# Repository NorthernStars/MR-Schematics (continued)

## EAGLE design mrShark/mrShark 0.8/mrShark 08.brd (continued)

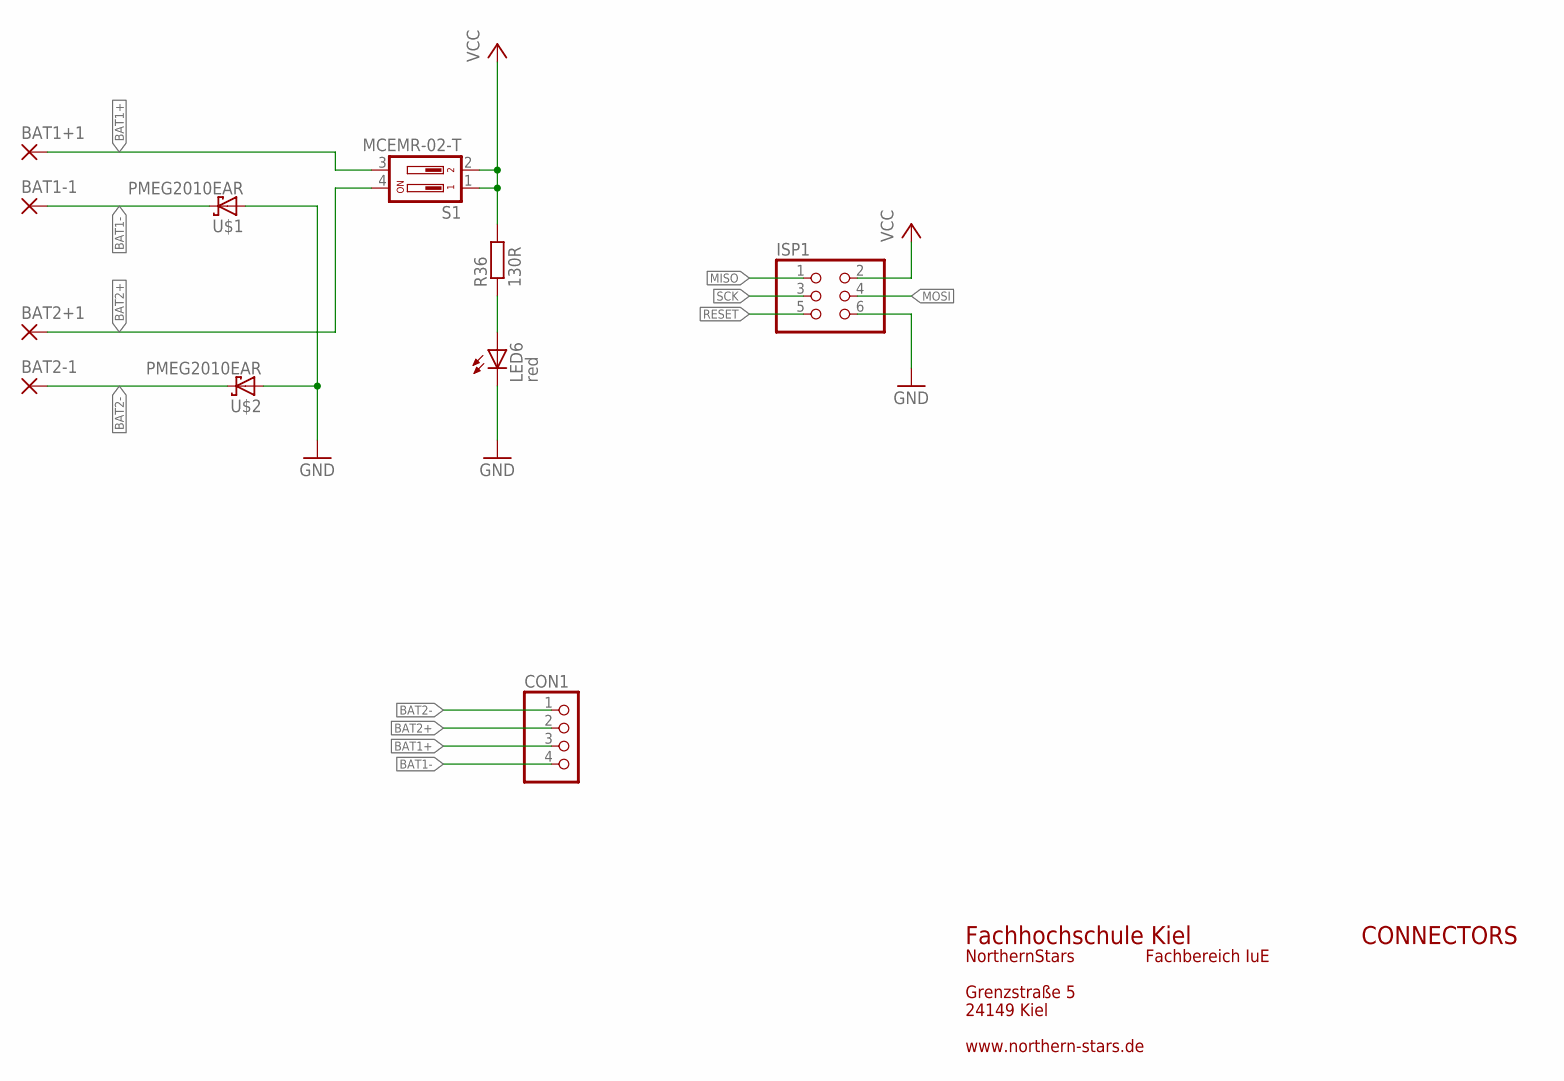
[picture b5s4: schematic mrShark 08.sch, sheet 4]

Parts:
BAT1+1, BAT1-1, BAT2+1, BAT2-1: 1,6/0,9
CON1: PINHD-1X04_2.54-SMD-90°; 1X04SMD/90
ISP1: PINHD-2X03_2.54-SMD; 2X03SMD
LED6: red; CHIPLED_1206
R36: 130R; R1206
S1: MCEMR-02-T; CTS-219-02
U$1, U$2: PMEG2010EAR; SOD323-R

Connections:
BAT1+: BAT1+1.1, CON1.3, S1.3
BAT1-: BAT1-1.1, CON1.4, U$1.C
BAT2+: BAT2+1.1, CON1.2, S1.4
BAT2-: BAT2-1.1, CON1.1, U$2.C
GND: ISP1.6, LED6.C, U$1.A, U$2.A; also elsewhere on the board
MISO: ISP1.1; also elsewhere on the board
MOSI: ISP1.4; also elsewhere on the board
unnamed: LED6.A, R36.1
RESET: ISP1.5; also elsewhere on the board
SCK: ISP1.3; also elsewhere on the board
VCC: ISP1.2, R36.2, S1.1, S1.2; also elsewhere on the board

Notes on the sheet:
CONNECTORS
Fachhochschule Kiel
Grenzstraße 5
24149 Kiel
NorthernStars
Fachbereich IuE
www.northern-stars.de

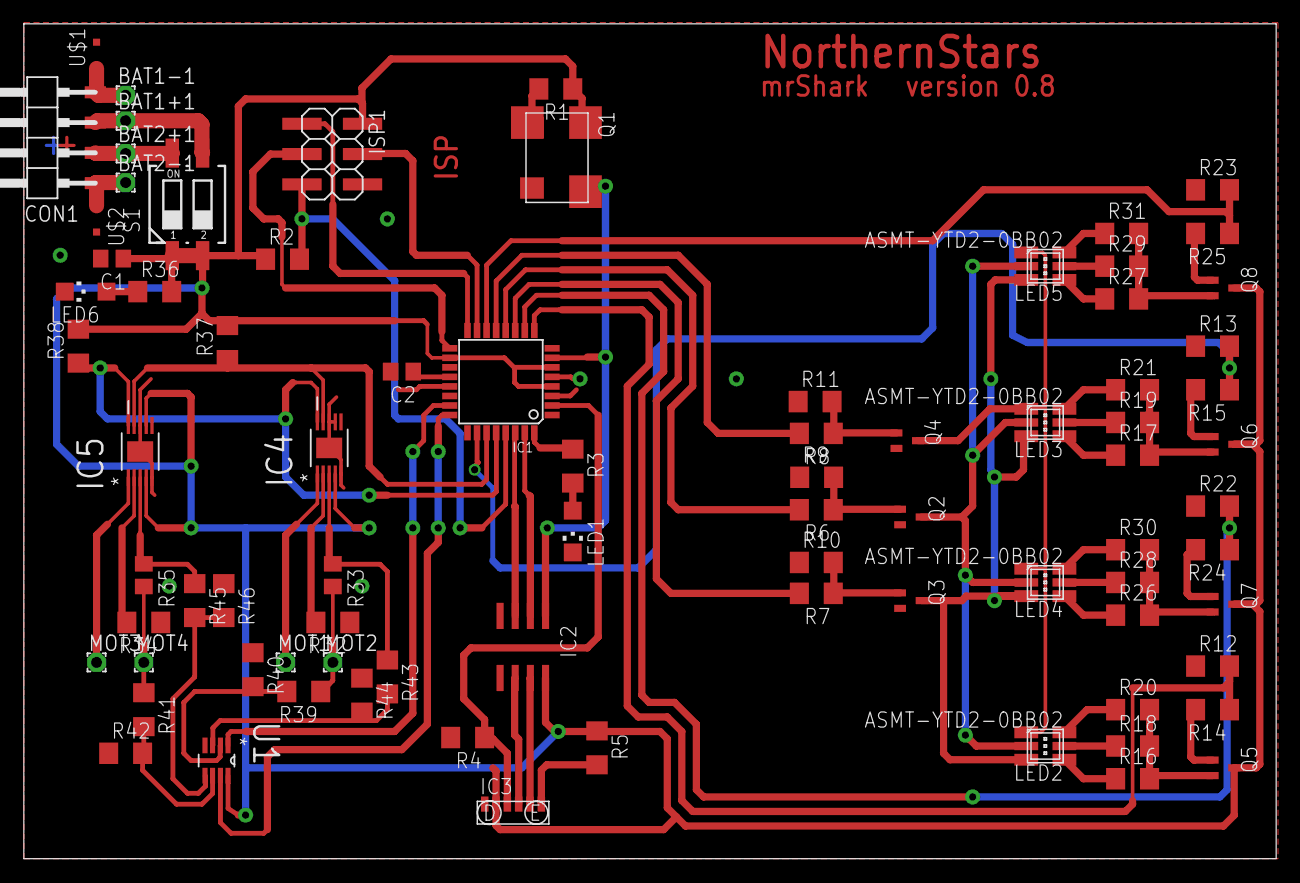
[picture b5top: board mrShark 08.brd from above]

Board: 2 copper layers, 105.0 x 70.0 mm, 81 parts (0 on the bottom side), 71 nets.

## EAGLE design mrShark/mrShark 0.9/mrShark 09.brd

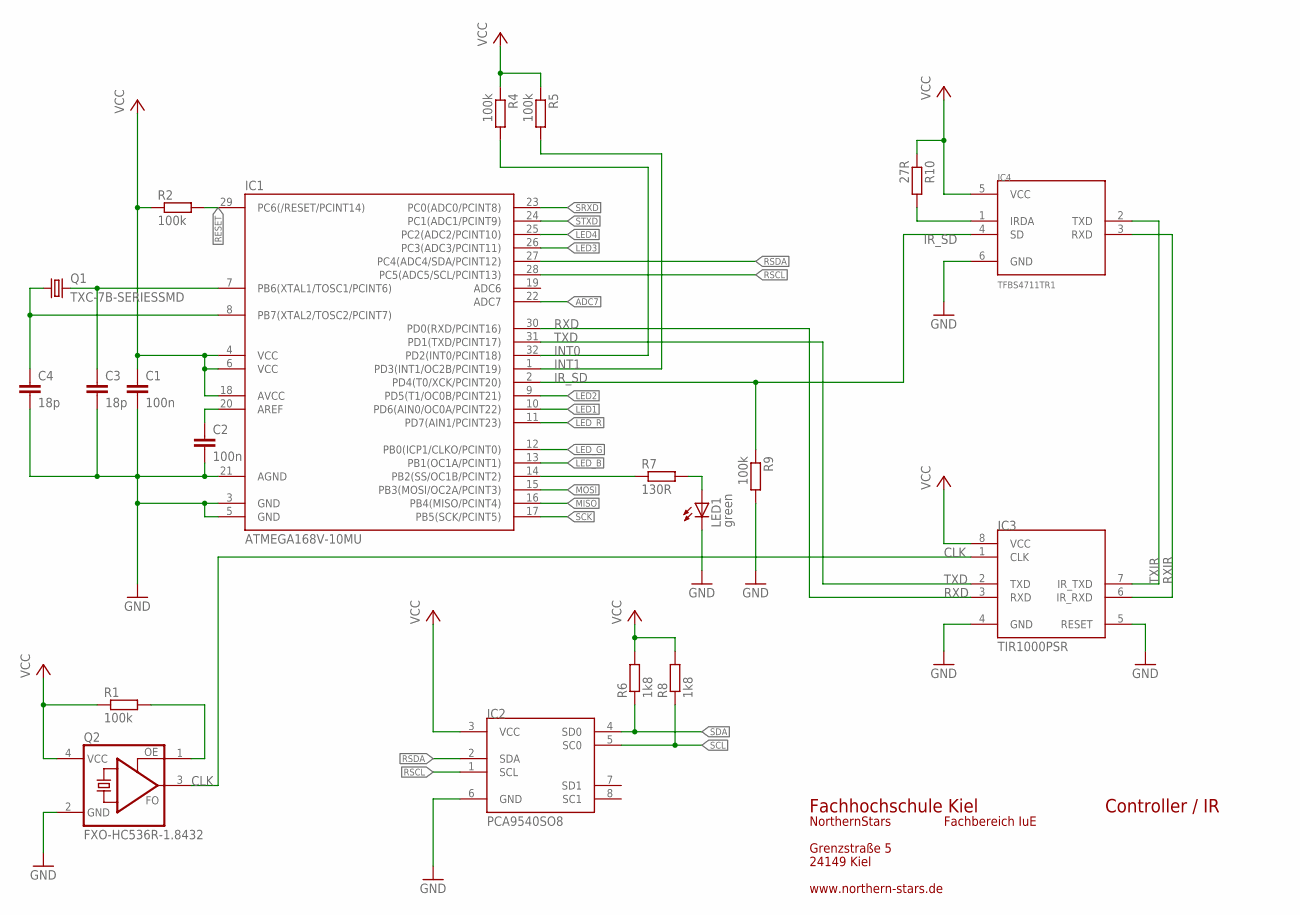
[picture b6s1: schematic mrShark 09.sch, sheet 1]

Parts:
C1, C2: 100n; C1206
C3, C4: 18p; C0805
IC1: ATMEGA168V-10MU; TQFP32-08
IC2: PCA9540SO8; SO8
IC3: TIR1000PSR; SO-08
IC4: TFBS4711TR1; TFBS4711
LED1: green; CHIPLED_0603
Q1: TXC-7B-SERIESSMD; TXC_7B_SERIES
Q2: FXO-HC536R-1.8432; HC536
R1, R2, R4, R5, R9: 100k; R1206
R6, R8: 1k8; R1206
R7: 130R; R1206
R10: 27R; R1206

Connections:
ADC7: IC1.22 (ADC7); also elsewhere on the board
CLK: IC3.1 (CLK), Q2.3 (FO)
GND: C1.2, C2.2, C3.2, C4.2, IC1.3 (GND), IC1.5 (GND), IC1.21 (AGND), IC2.6 (GND), IC3.4 (GND), IC3.5 (RESET), IC4.6 (GND), LED1.C, Q2.2 (GND), R9.2; also elsewhere on the board
INT0: IC1.32 (PD2(INT0/PCINT18)), R4.2; also elsewhere on the board
INT1: IC1.1 (PD3(INT1/OC2B/PCINT19)), R5.2; also elsewhere on the board
IRDA: IC4.1 (IRDA), R10.2
IR_SD: IC1.2 (PD4(T0/XCK/PCINT20)), IC4.4 (SD), R9.1
LED1: IC1.10 (PD6(AIN0/OC0A/PCINT22)); also elsewhere on the board
LED2: IC1.9 (PD5(T1/OC0B/PCINT21)); also elsewhere on the board
LED3: IC1.26 (PC3(ADC3/PCINT11)); also elsewhere on the board
LED4: IC1.25 (PC2(ADC2/PCINT10)); also elsewhere on the board
LED_B: IC1.13 (PB1(OC1A/PCINT1)); also elsewhere on the board
LED_G: IC1.12 (PB0(ICP1/CLKO/PCINT0)); also elsewhere on the board
LED_R: IC1.11 (PD7(AIN1/PCINT23)); also elsewhere on the board
MISO: IC1.16 (PB4(MISO/PCINT4)); also elsewhere on the board
MOSI: IC1.15 (PB3(MOSI/OC2A/PCINT3)); also elsewhere on the board
unnamed: IC1.14 (PB2(SS/OC1B/PCINT2)), R7.1
unnamed: Q2.1 (OE), R1.2
unnamed: LED1.A, R7.2
unnamed: C3.1, IC1.7 (PB6(XTAL1/TOSC1/PCINT6)), Q1.3 (2)
unnamed: C4.1, IC1.8 (PB7(XTAL2/TOSC2/PCINT7)), Q1.1
unnamed: C2.1, IC1.20 (AREF)
RESET: IC1.29 (PC6(/RESET/PCINT14)), R2.2; also elsewhere on the board
RSCL: IC1.28 (PC5(ADC5/SCL/PCINT13)), IC2.1 (SCL); also elsewhere on the board
RSDA: IC1.27 (PC4(ADC4/SDA/PCINT12)), IC2.2 (SDA); also elsewhere on the board
RXD: IC1.30 (PD0(RXD/PCINT16)), IC3.3 (RXD)
RXIR: IC3.6 (IR_RXD), IC4.3 (RXD)
SCK: IC1.17 (PB5(SCK/PCINT5)); also elsewhere on the board
SCL: IC2.5 (SC0), R8.1; also elsewhere on the board
SDA: IC2.4 (SD0), R6.1; also elsewhere on the board
SRXD: IC1.23 (PC0(ADC0/PCINT8)); also elsewhere on the board
STXD: IC1.24 (PC1(ADC1/PCINT9)); also elsewhere on the board
TXD: IC1.31 (PD1(TXD/PCINT17)), IC3.2 (TXD)
TXIR: IC3.7 (IR_TXD), IC4.2 (TXD)
VCC: C1.1, IC1.4 (VCC), IC1.6 (VCC), IC1.18 (AVCC), IC2.3 (VCC), IC3.8 (VCC), IC4.5 (VCC), Q2.4 (VCC), R1.1, R2.1, R4.1, R5.1, R6.2, R8.2, R10.1; also elsewhere on the board

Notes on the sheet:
Fachhochschule Kiel
Grenzstraße 5
24149 Kiel
NorthernStars
Fachbereich IuE
www.northern-stars.de
Controller / IR

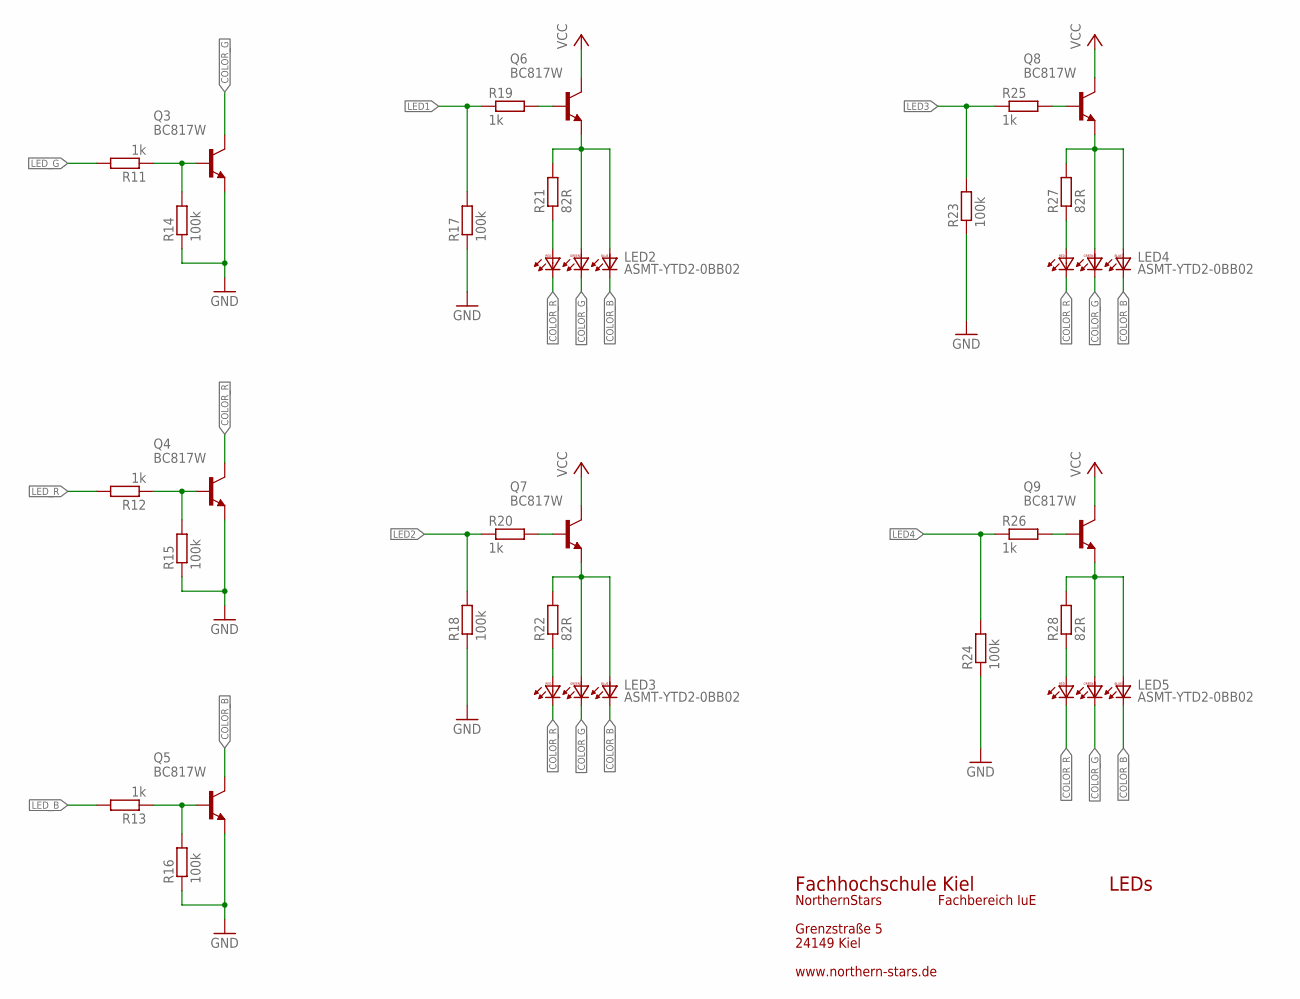
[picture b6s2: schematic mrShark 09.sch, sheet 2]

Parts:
LED2, LED3, LED4, LED5: ASMT-YTD2-0BB02; PLCC6K
Q3, Q4, Q5, Q6, Q7, Q8, Q9: BC817W; SOT323-BEC
R11, R12, R13, R19, R20, R25, R26: 1k; R1206
R14, R15, R16, R17, R18, R23, R24: 100k; R1206
R21, R22, R27, R28: 82R; R1206

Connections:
COLOR_B: LED2.1 (BC), LED3.1 (BC), LED4.1 (BC), LED5.1 (BC), Q5.C
COLOR_G: LED2.2 (GC), LED3.2 (GC), LED4.2 (GC), LED5.2 (GC), Q3.C
COLOR_R: LED2.3 (RC), LED3.3 (RC), LED4.3 (RC), LED5.3 (RC), Q4.C
GND: Q3.E, Q4.E, Q5.E, R14.1, R15.1, R16.1, R17.1, R18.1, R23.1, R24.1; also elsewhere on the board
LED1: R17.2, R19.1; also elsewhere on the board
LED2: R18.2, R20.1; also elsewhere on the board
LED3: R23.2, R25.1; also elsewhere on the board
LED4: R24.2, R26.1; also elsewhere on the board
LED_B: R13.2; also elsewhere on the board
LED_G: R11.2; also elsewhere on the board
LED_R: R12.2; also elsewhere on the board
unnamed: LED2.4 (RA), R21.1
unnamed: LED4.4 (RA), R27.1
unnamed: LED4.5 (GA), LED4.6 (BA), Q8.E, R27.2
unnamed: LED3.4 (RA), R22.1
unnamed: LED3.5 (GA), LED3.6 (BA), Q7.E, R22.2
unnamed: Q7.B, R20.2
unnamed: LED5.4 (RA), R28.1
unnamed: LED5.5 (GA), LED5.6 (BA), Q9.E, R28.2
unnamed: Q9.B, R26.2
unnamed: Q8.B, R25.2
unnamed: Q6.B, R19.2
unnamed: LED2.5 (GA), LED2.6 (BA), Q6.E, R21.2
VCC: Q6.C, Q7.C, Q8.C, Q9.C; also elsewhere on the board
X1: Q5.B, R13.1, R16.2
X2: Q4.B, R12.1, R15.2
X3: Q3.B, R11.1, R14.2

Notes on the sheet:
LEDs
Fachhochschule Kiel
Grenzstraße 5
24149 Kiel
NorthernStars
Fachbereich IuE
www.northern-stars.de

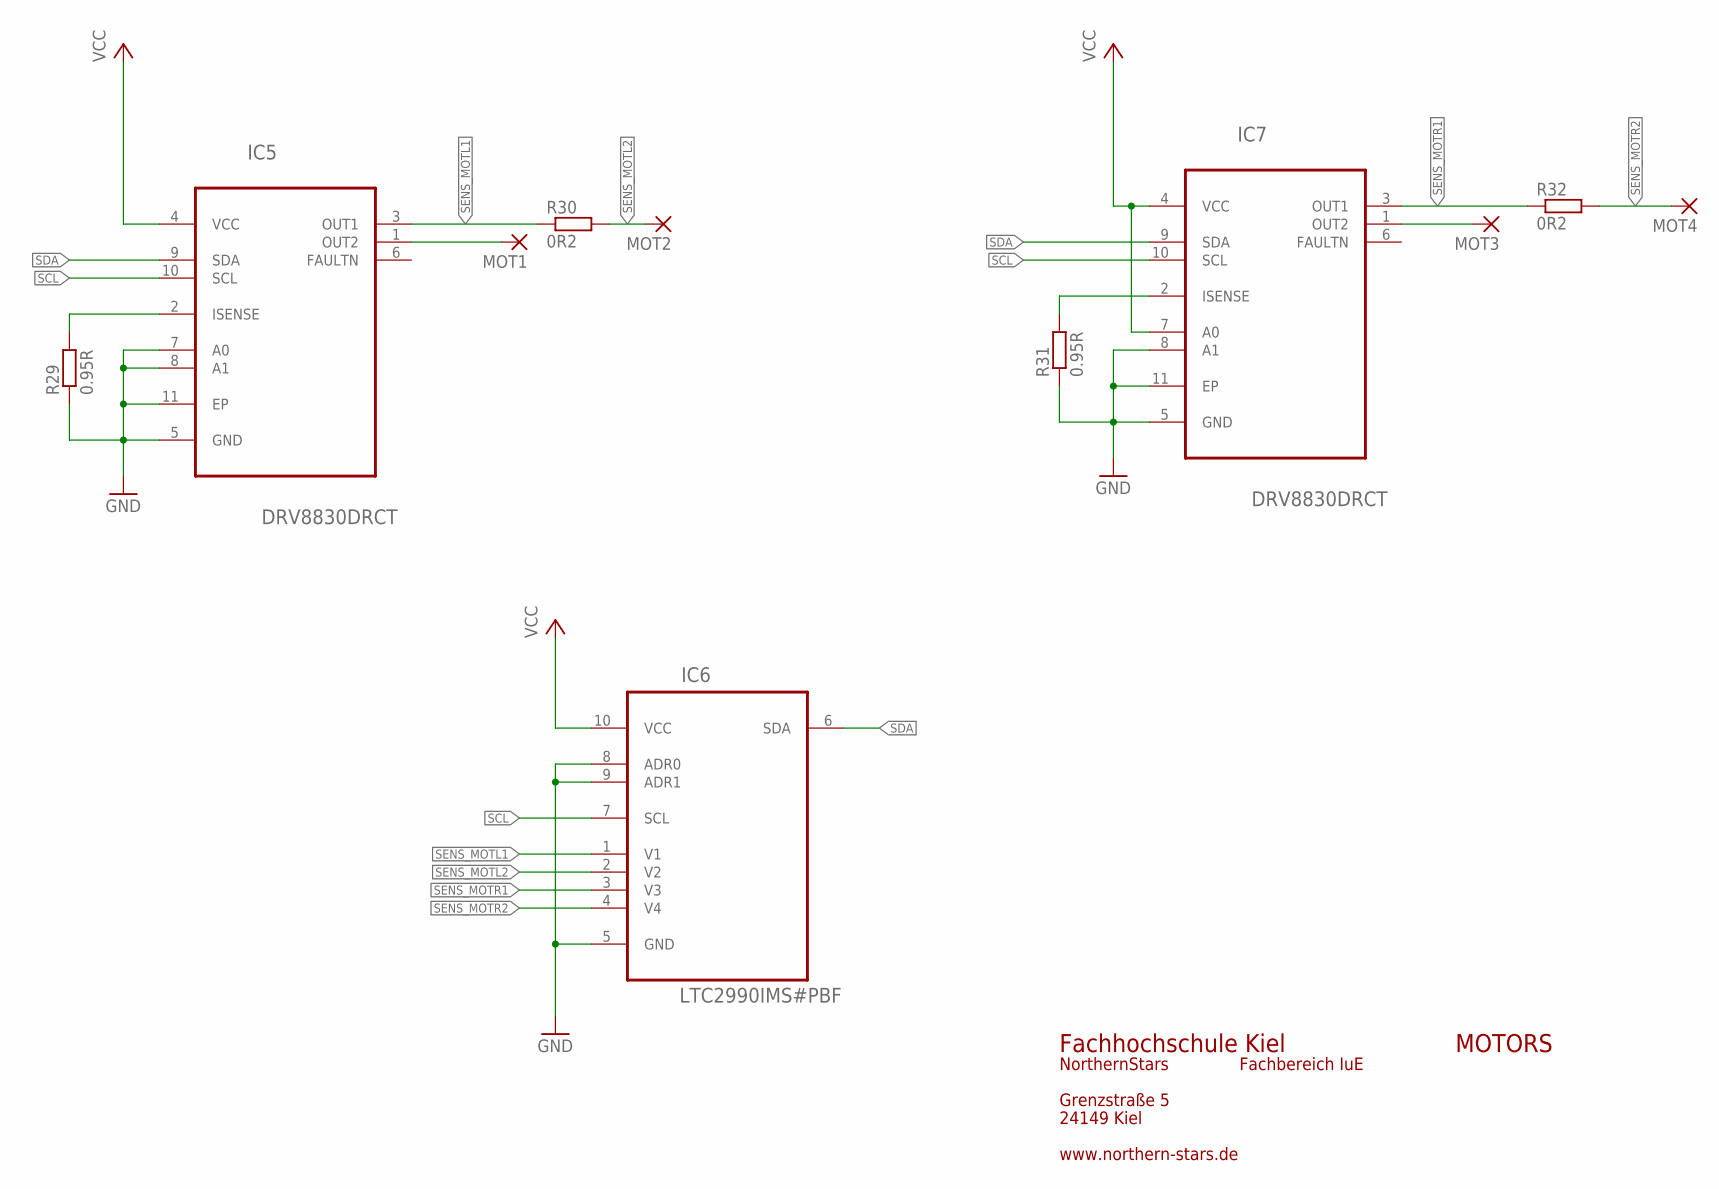
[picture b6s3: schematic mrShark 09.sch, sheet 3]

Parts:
IC5, IC7: DRV8830DRCT; SOP65P640X110-15N
IC6: LTC2990IMS#PBF; SOP50P490X110-10N
MOT1, MOT2, MOT3, MOT4: SMD5; SMD2,54-5,08
R29, R31: 0.95R; R1206
R30, R32: 0R2; R1206

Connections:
GND: IC5.5 (GND), IC5.7 (A0), IC5.8 (A1), IC5.11 (EP), IC6.5 (GND), IC6.8 (ADR0), IC6.9 (ADR1), IC7.5 (GND), IC7.8 (A1), IC7.11 (EP), R29.1, R31.1; also elsewhere on the board
unnamed: IC5.1 (OUT2), MOT1.1
unnamed: IC5.2 (ISENSE), R29.2
unnamed: IC7.1 (OUT2), MOT3.1
unnamed: IC7.2 (ISENSE), R31.2
SCL: IC5.10 (SCL), IC6.7 (SCL), IC7.10 (SCL); also elsewhere on the board
SDA: IC5.9 (SDA), IC6.6 (SDA), IC7.9 (SDA); also elsewhere on the board
SENS_MOTL1: IC5.3 (OUT1), IC6.1 (V1), R30.1
SENS_MOTL2: IC6.2 (V2), MOT2.1, R30.2
SENS_MOTR1: IC6.3 (V3), IC7.3 (OUT1), R32.1
SENS_MOTR2: IC6.4 (V4), MOT4.1, R32.2
VCC: IC5.4 (VCC), IC6.10 (VCC), IC7.4 (VCC), IC7.7 (A0); also elsewhere on the board

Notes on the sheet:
MOTORS
Fachhochschule Kiel
Grenzstraße 5
24149 Kiel
NorthernStars
Fachbereich IuE
www.northern-stars.de

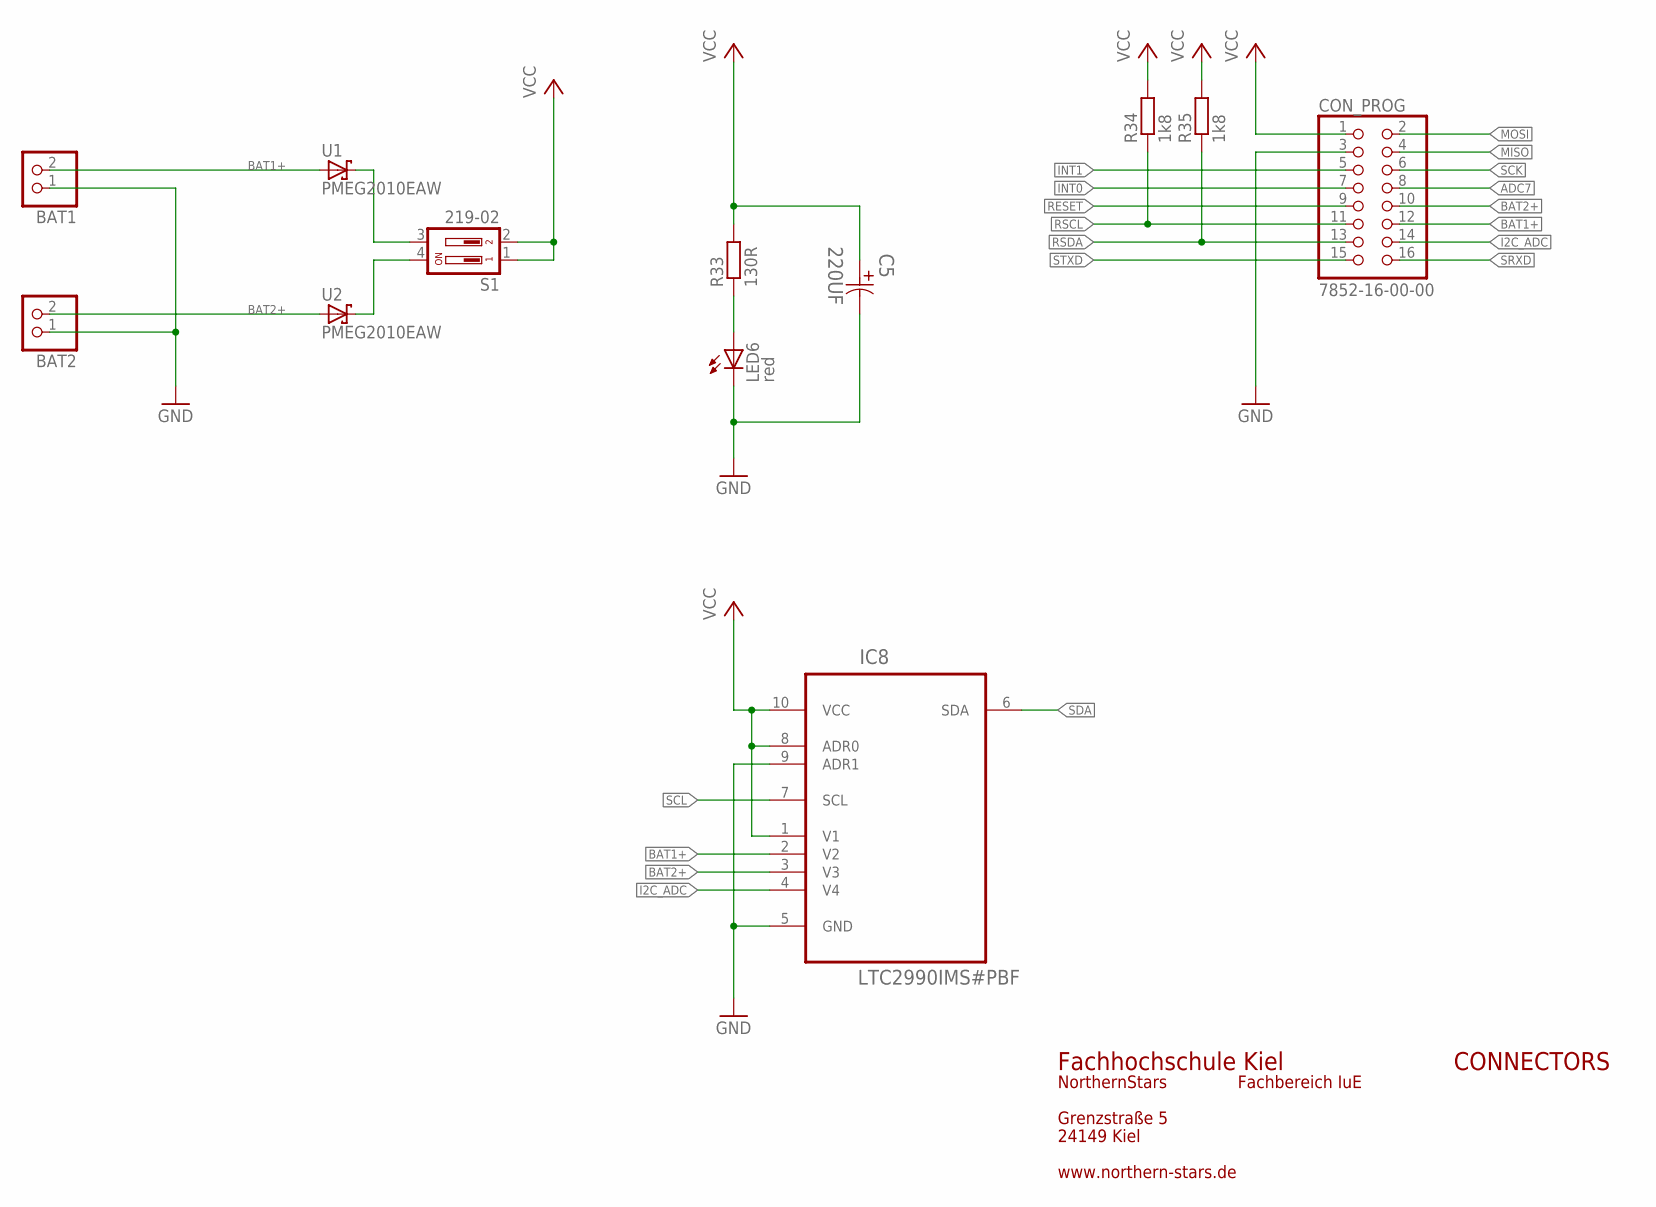
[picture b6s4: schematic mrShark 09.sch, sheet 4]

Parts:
BAT1, BAT2: PINHD-1X02_2.54-SMD; 1X02SMD
C5: 220UF; CAPAE660X800N
CON_PROG: 7852-16-00-00; 2X08SMD
IC8: LTC2990IMS#PBF; SOP50P490X110-10N
LED6: red; CHIPLED_0603
R33: 130R; R1206
R34, R35: 1k8; R1206
S1: 219-02; CTS-219-02
U1, U2: PMEG2010EAW; SOD323-W

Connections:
ADC7: CON_PROG.8; also elsewhere on the board
BAT1+: BAT1.2, CON_PROG.12, IC8.2 (V2), U1.A
BAT2+: BAT2.2, CON_PROG.10, IC8.3 (V3), U2.A
GND: BAT1.1, BAT2.1, C5.2, CON_PROG.3, IC8.5 (GND), IC8.9 (ADR1), LED6.C; also elsewhere on the board
I2C_ADC: CON_PROG.14, IC8.4 (V4)
INT0: CON_PROG.7; also elsewhere on the board
INT1: CON_PROG.5; also elsewhere on the board
MISO: CON_PROG.4; also elsewhere on the board
MOSI: CON_PROG.2; also elsewhere on the board
unnamed: S1.3, U1.C
unnamed: S1.4, U2.C
unnamed: LED6.A, R33.1
RESET: CON_PROG.9; also elsewhere on the board
RSCL: CON_PROG.11, R34.1; also elsewhere on the board
RSDA: CON_PROG.13, R35.1; also elsewhere on the board
SCK: CON_PROG.6; also elsewhere on the board
SCL: IC8.7 (SCL); also elsewhere on the board
SDA: IC8.6 (SDA); also elsewhere on the board
SRXD: CON_PROG.16; also elsewhere on the board
STXD: CON_PROG.15; also elsewhere on the board
VCC: C5.1, CON_PROG.1, IC8.1 (V1), IC8.8 (ADR0), IC8.10 (VCC), R33.2, R34.2, R35.2, S1.1, S1.2; also elsewhere on the board

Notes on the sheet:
CONNECTORS
Fachhochschule Kiel
Grenzstraße 5
24149 Kiel
NorthernStars
Fachbereich IuE
www.northern-stars.de

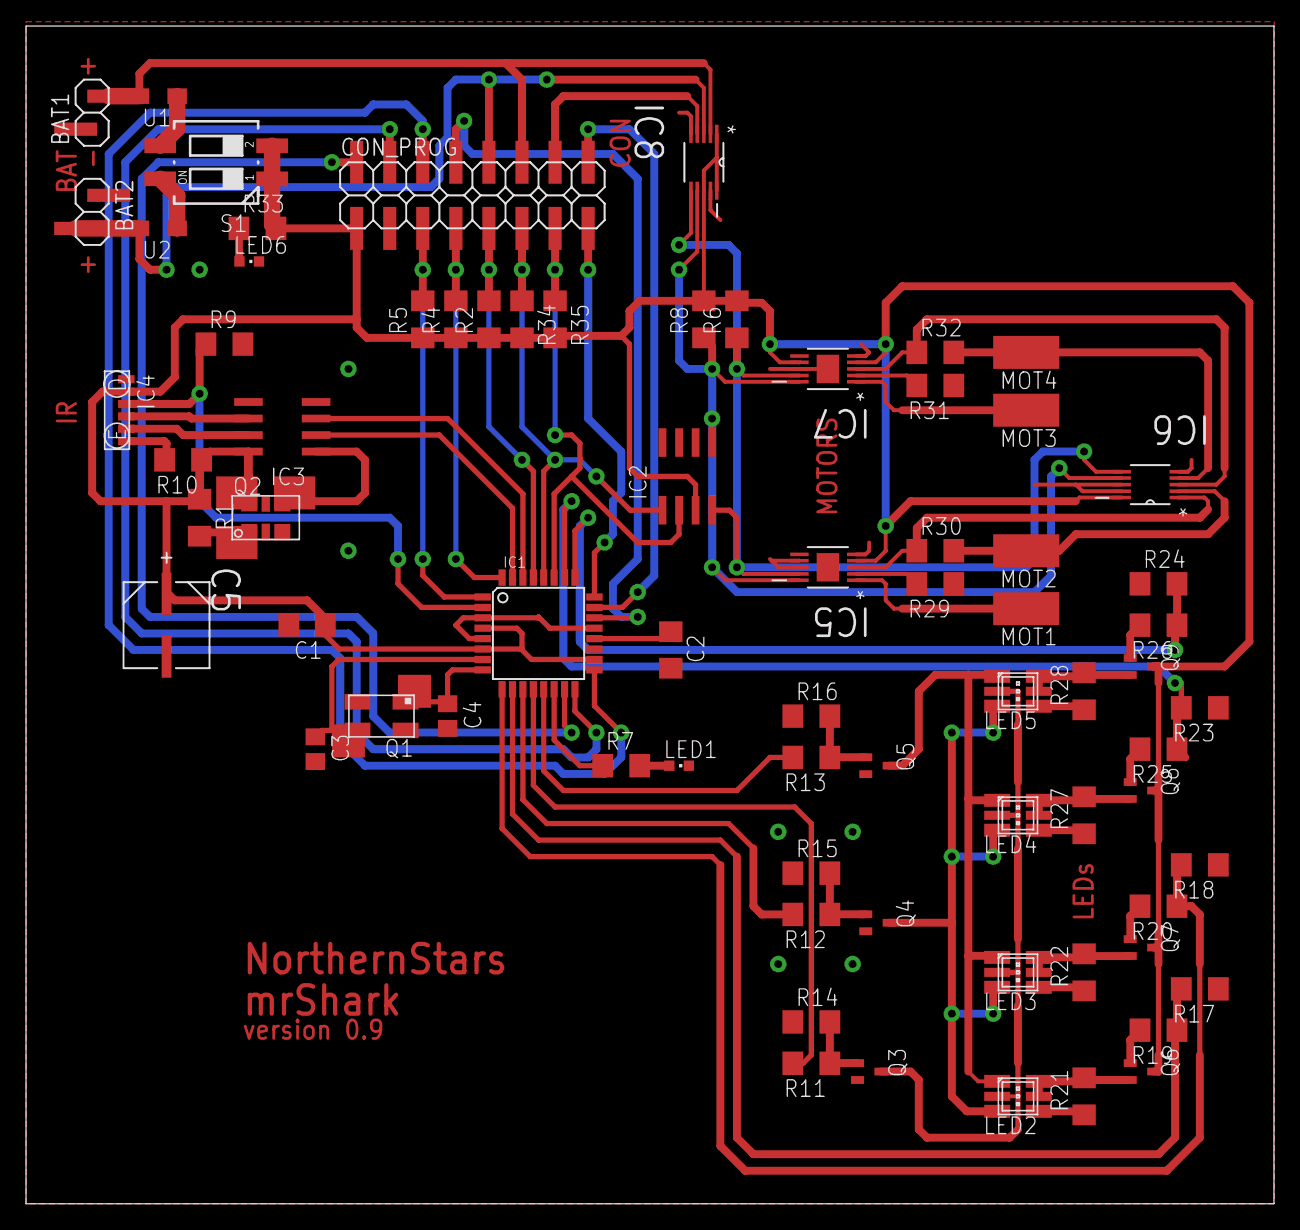
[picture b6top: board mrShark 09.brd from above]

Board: 2 copper layers, 95.9 x 90.5 mm, 72 parts (0 on the bottom side), 67 nets.

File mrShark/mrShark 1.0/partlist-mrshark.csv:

sep=;
Quantity;Partname;Value;Package
2; C1, C2; 100n; C0201
2; C3, C4; 18p; C0201
1; CON_PROG; DF12(5.0)-20DP-0.5V; DF12-20DP
2; D1, D2; PMEG2010EA; SOD323-R
1; IC1; ATMEGA168V-10MU; MLF32
1; IC2; PCA9540B; TSSOP8
1; IC3; TIR1000PWR; PW_R-PDSO-G08
1; IC4; TFBS4711TR1; TFBS4711
2; IC5, IC7; DRV8830DRCT; S-PDSO-N10
2; IC6, IC8; LTC2990IMS#PBF; SOP50P490X110-10N
1; LED1; green; CHIPLED_0603
4; LED2, LED3, LED4, LED5; ASMT-YTD2-0BB02; PLCC6K
1; LED6; red; CHIPLED_0603
1; Q1; FXO-HC536R-1.8432 ; 3.2X2.5
7; Q2, Q3, Q4, Q5, Q6, Q7, Q8; BC817W; SOT323-BEC
1; Q9; 11.0592MHZ; TXC_7B_SERIES
12; R1, R2, R4, R5, R9, R14, R15, R16, R17, R18, R23, R24; 100k; R0201
6; R6, R21, R22, R27, R28, R33; 130R; R0201
4; R7, R8, R34, R35; 1k8; R0201
1; R10; 27R; R0201
2; R11, R13; 2k; R0201
1; R12; 1k; R0201
4; R19, R20, R25, R26; 560R; R0201
2; R29, R31; 0.95R; R0603
2; R30, R32; 0R2; R0603
1; SWITCH_PWR; AYZ0202AGRLC; AYZ0202AGLRC

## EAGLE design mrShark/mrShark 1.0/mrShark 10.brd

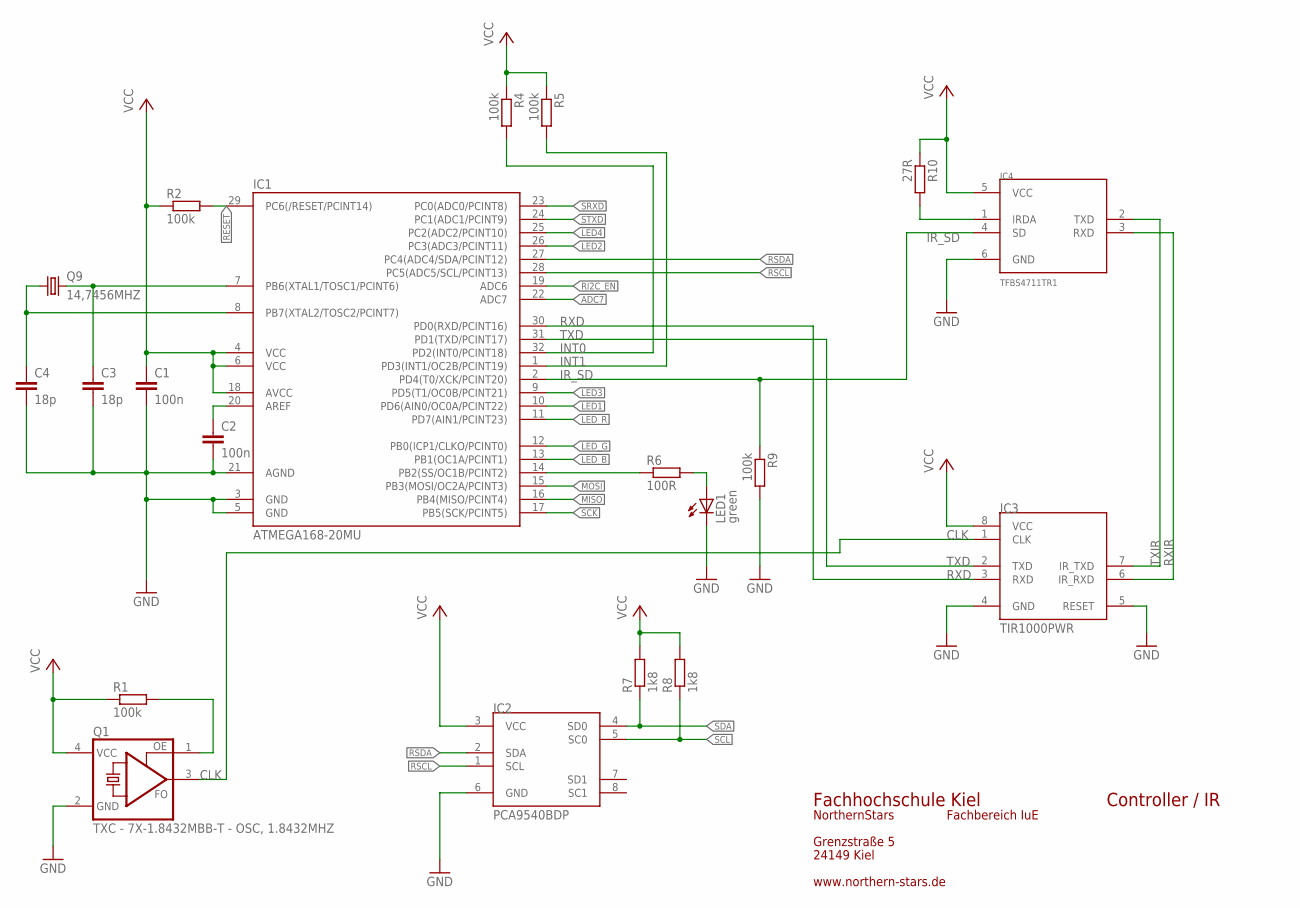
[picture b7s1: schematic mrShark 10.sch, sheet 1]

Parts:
C1, C2: 100n; C0201
C3, C4: 18p; C0201
IC1: ATMEGA168-20MU; MLF32
IC2: PCA9540BDP; TSSOP8
IC3: TIR1000PWR; PW_R-PDSO-G08
IC4: TFBS4711TR1; TFBS4711
LED1: green; CHIPLED_0603
Q1: TXC - 7X-1.8432MBB-T - OSC, 1.8432MHZ; 3.2X2.5
Q9: 14,7456MHZ; TXC_7B_SERIES
R1, R2, R4, R5, R9: 100k; R0201
R6: 100R; R0201
R7, R8: 1k8; R0201
R10: 27R; R0201

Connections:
ADC7: IC1.22 (ADC7); also elsewhere on the board
CLK: IC3.1 (CLK), Q1.3 (FO)
GND: C1.2, C2.2, C3.2, C4.2, IC1.3 (GND), IC1.5 (GND), IC1.21 (AGND), IC2.6 (GND), IC3.4 (GND), IC3.5 (RESET), IC4.6 (GND), LED1.C, Q1.2 (GND), R9.2; also elsewhere on the board
INT0: IC1.32 (PD2(INT0/PCINT18)), R4.2; also elsewhere on the board
INT1: IC1.1 (PD3(INT1/OC2B/PCINT19)), R5.2; also elsewhere on the board
IRDA: IC4.1 (IRDA), R10.2
IR_SD: IC1.2 (PD4(T0/XCK/PCINT20)), IC4.4 (SD), R9.1
LED1: IC1.10 (PD6(AIN0/OC0A/PCINT22)); also elsewhere on the board
LED2: IC1.26 (PC3(ADC3/PCINT11)); also elsewhere on the board
LED3: IC1.9 (PD5(T1/OC0B/PCINT21)); also elsewhere on the board
LED4: IC1.25 (PC2(ADC2/PCINT10)); also elsewhere on the board
LED_B: IC1.13 (PB1(OC1A/PCINT1)); also elsewhere on the board
LED_G: IC1.12 (PB0(ICP1/CLKO/PCINT0)); also elsewhere on the board
LED_R: IC1.11 (PD7(AIN1/PCINT23)); also elsewhere on the board
MISO: IC1.16 (PB4(MISO/PCINT4)); also elsewhere on the board
MOSI: IC1.15 (PB3(MOSI/OC2A/PCINT3)); also elsewhere on the board
unnamed: IC1.14 (PB2(SS/OC1B/PCINT2)), R6.1
unnamed: Q1.1 (OE), R1.2
unnamed: LED1.A, R6.2
unnamed: C2.1, IC1.20 (AREF)
RESET: IC1.29 (PC6(/RESET/PCINT14)), R2.2; also elsewhere on the board
RI2C_EN: IC1.19 (ADC6)
RSCL: IC1.28 (PC5(ADC5/SCL/PCINT13)), IC2.1 (SCL); also elsewhere on the board
RSDA: IC1.27 (PC4(ADC4/SDA/PCINT12)), IC2.2 (SDA); also elsewhere on the board
RXD: IC1.30 (PD0(RXD/PCINT16)), IC3.3 (RXD)
RXIR: IC3.6 (IR_RXD), IC4.3 (RXD)
SCK: IC1.17 (PB5(SCK/PCINT5)); also elsewhere on the board
SCL: IC2.5 (SC0), R8.1; also elsewhere on the board
SDA: IC2.4 (SD0), R7.1; also elsewhere on the board
SRXD: IC1.23 (PC0(ADC0/PCINT8)); also elsewhere on the board
STXD: IC1.24 (PC1(ADC1/PCINT9)); also elsewhere on the board
TXD: IC1.31 (PD1(TXD/PCINT17)), IC3.2 (TXD)
TXIR: IC3.7 (IR_TXD), IC4.2 (TXD)
VCC: C1.1, IC1.4 (VCC), IC1.6 (VCC), IC1.18 (AVCC), IC2.3 (VCC), IC3.8 (VCC), IC4.5 (VCC), Q1.4 (VCC), R1.1, R2.1, R4.1, R5.1, R7.2, R8.2, R10.1; also elsewhere on the board
XTAL1: C3.1, IC1.7 (PB6(XTAL1/TOSC1/PCINT6)), Q9.3 (2)
XTAL2: C4.1, IC1.8 (PB7(XTAL2/TOSC2/PCINT7)), Q9.1

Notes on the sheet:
Fachhochschule Kiel
Grenzstraße 5
24149 Kiel
NorthernStars
Fachbereich IuE
www.northern-stars.de
Controller / IR

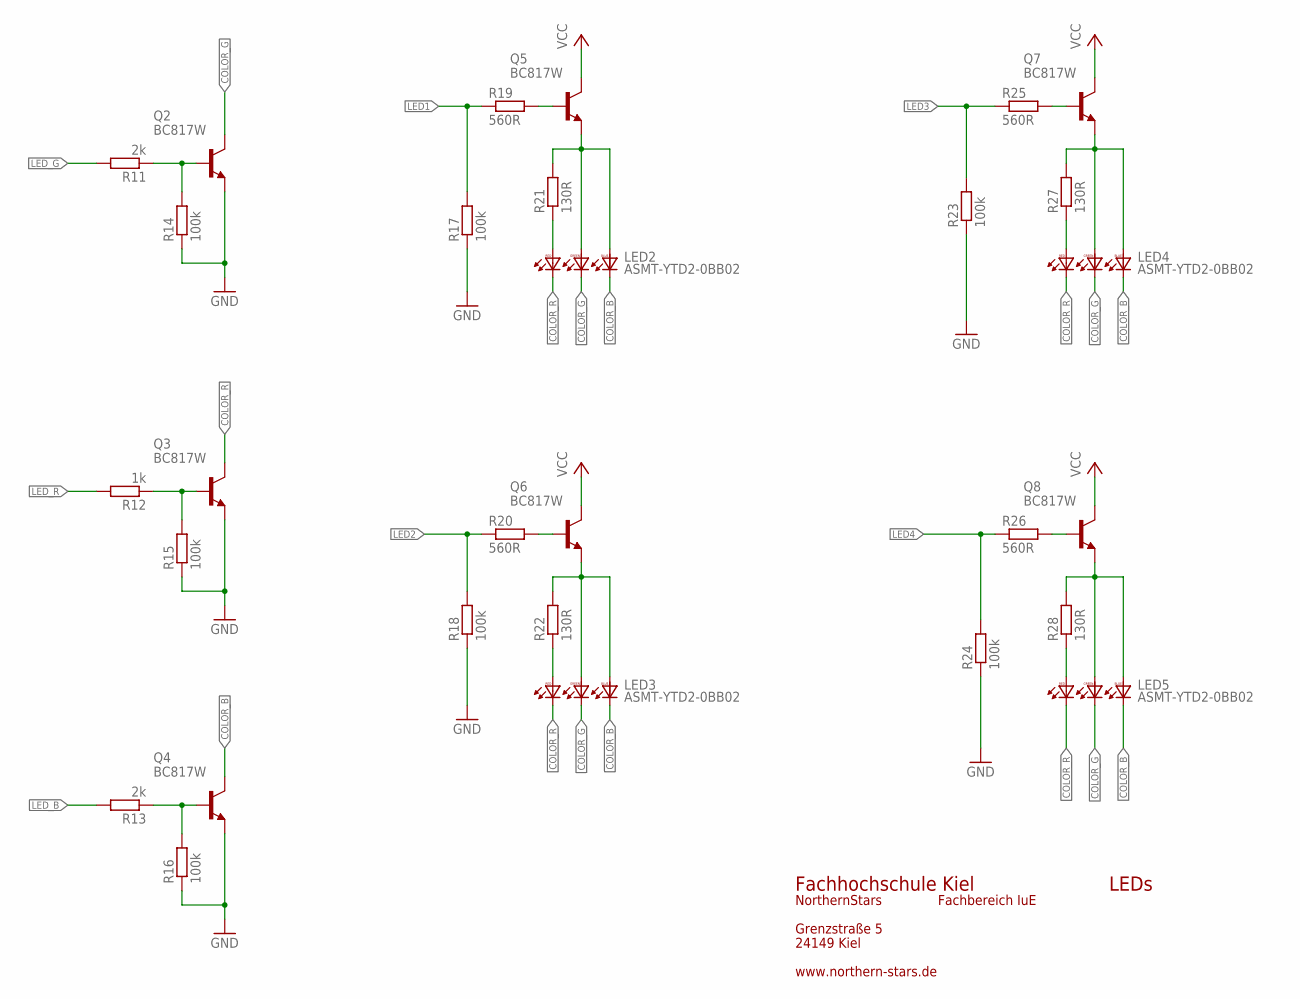
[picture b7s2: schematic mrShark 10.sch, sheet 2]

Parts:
LED2, LED3, LED4, LED5: ASMT-YTD2-0BB02; PLCC6K
Q2, Q3, Q4, Q5, Q6, Q7, Q8: BC817W; SOT323-BEC
R11, R13: 2k; R0201
R12: 1k; R0201
R14, R15, R16, R17, R18, R23, R24: 100k; R0201
R19, R20, R25, R26: 560R; R0201
R21, R22, R27, R28: 130R; R0201

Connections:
COLOR_B: LED2.1 (BC), LED3.1 (BC), LED4.1 (BC), LED5.1 (BC), Q4.C
COLOR_G: LED2.2 (GC), LED3.2 (GC), LED4.2 (GC), LED5.2 (GC), Q2.C
COLOR_R: LED2.3 (RC), LED3.3 (RC), LED4.3 (RC), LED5.3 (RC), Q3.C
GND: Q2.E, Q3.E, Q4.E, R14.1, R15.1, R16.1, R17.1, R18.1, R23.1, R24.1; also elsewhere on the board
LED1: R17.2, R19.1; also elsewhere on the board
LED2: R18.2, R20.1; also elsewhere on the board
LED3: R23.2, R25.1; also elsewhere on the board
LED4: R24.2, R26.1; also elsewhere on the board
LED_B: R13.2; also elsewhere on the board
LED_G: R11.2; also elsewhere on the board
LED_R: R12.2; also elsewhere on the board
unnamed: LED2.4 (RA), R21.1
unnamed: LED4.4 (RA), R27.1
unnamed: LED4.5 (GA), LED4.6 (BA), Q7.E, R27.2
unnamed: LED3.4 (RA), R22.1
unnamed: LED3.5 (GA), LED3.6 (BA), Q6.E, R22.2
unnamed: Q6.B, R20.2
unnamed: LED5.4 (RA), R28.1
unnamed: LED5.5 (GA), LED5.6 (BA), Q8.E, R28.2
unnamed: Q8.B, R26.2
unnamed: Q7.B, R25.2
unnamed: Q5.B, R19.2
unnamed: LED2.5 (GA), LED2.6 (BA), Q5.E, R21.2
VCC: Q5.C, Q6.C, Q7.C, Q8.C; also elsewhere on the board
X1: Q4.B, R13.1, R16.2
X2: Q3.B, R12.1, R15.2
X3: Q2.B, R11.1, R14.2

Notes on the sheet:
LEDs
Fachhochschule Kiel
Grenzstraße 5
24149 Kiel
NorthernStars
Fachbereich IuE
www.northern-stars.de
